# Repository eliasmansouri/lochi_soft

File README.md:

# lochi_soft IoT Environmental Monitoring Hackathon Challenge

## Overview

Welcome to our lochi_soft IoT Environmental Monitoring project, developed during the XYZ Hackathon Challenge. This project aims to measure temperature and air humidity, providing valuable insights into the environmental conditions of a given space. Although energy consumption data integration was a challenge we couldn't conquer during the hackathon, we've laid the groundwork for easy integration in the future.

## Features

- Real-time temperature and air humidity monitoring.
- Responsive web interface developed using NextJS.
- Easy integration for future energy consumption data.

## Getting Started

Follow these steps to get the project up and running:

1. **Clone the repository:**

   ```bash
   git clone https://github.com/your-username/lochi_soft.git
   ```

2. **Navigate to the project directory:**

   ```bash
    cd lochi_soft
   ```

3. **Install dependencies:**

   ```bash
   npm install
   ```

4. **Run the project:**

   ```bash
   npm run dev
   ```

5. **Access the web interface:**

   Open your browser and go to http://localhost:3000 to view the real-time environmental data.

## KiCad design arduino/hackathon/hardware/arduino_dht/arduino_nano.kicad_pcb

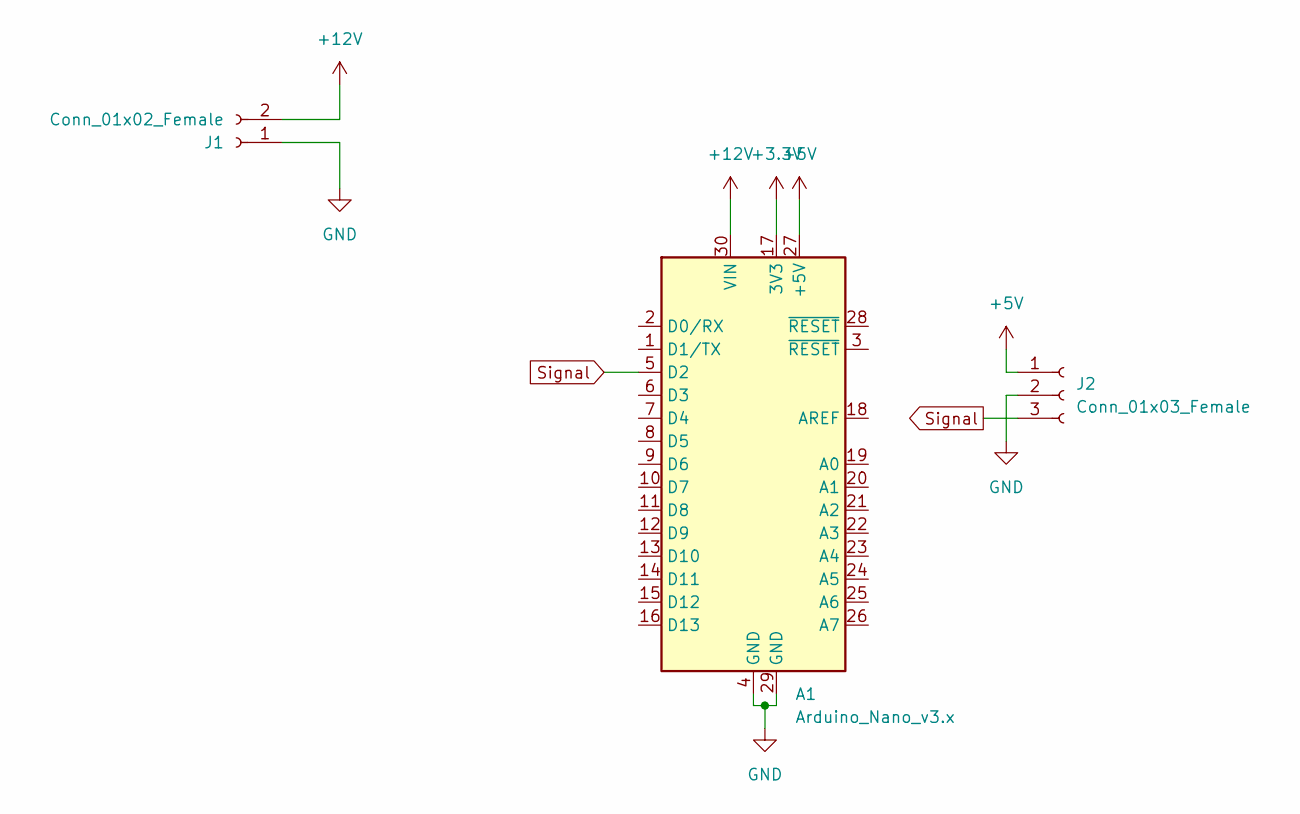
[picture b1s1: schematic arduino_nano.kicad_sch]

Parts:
A1: Arduino_Nano_v3.x; Arduino_Nano
J1: Conn_01x02_Female; Typ1
J2: Conn_01x03_Female; PinHeader_1x03_P2.54mm_Vertical

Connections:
+3.3V: A1.17 (3V3)
+5V: A1.27 (+5V), J2.1
+12V: A1.30 (VIN), J1.2
GND: A1.4 (GND), A1.29 (GND), J1.1, J2.2
Signal: A1.5 (D2), J2.3

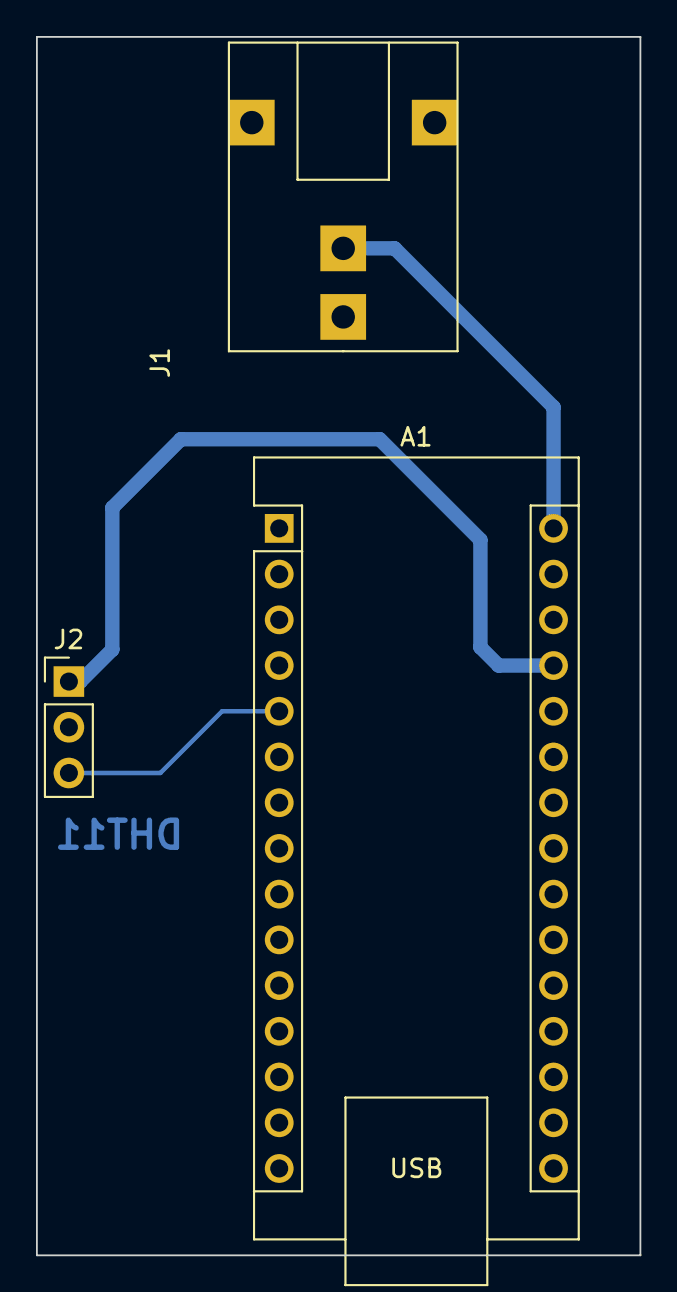
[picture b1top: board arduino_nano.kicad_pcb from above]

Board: 2 copper layers, 33.5 x 67.7 mm, 3 parts (0 on the bottom side), 4 nets.

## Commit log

2023-11-10 Initial commit from Create Next App
2023-11-11 second commit
2023-11-11 readme update
2023-11-11 hackaton arduino add
